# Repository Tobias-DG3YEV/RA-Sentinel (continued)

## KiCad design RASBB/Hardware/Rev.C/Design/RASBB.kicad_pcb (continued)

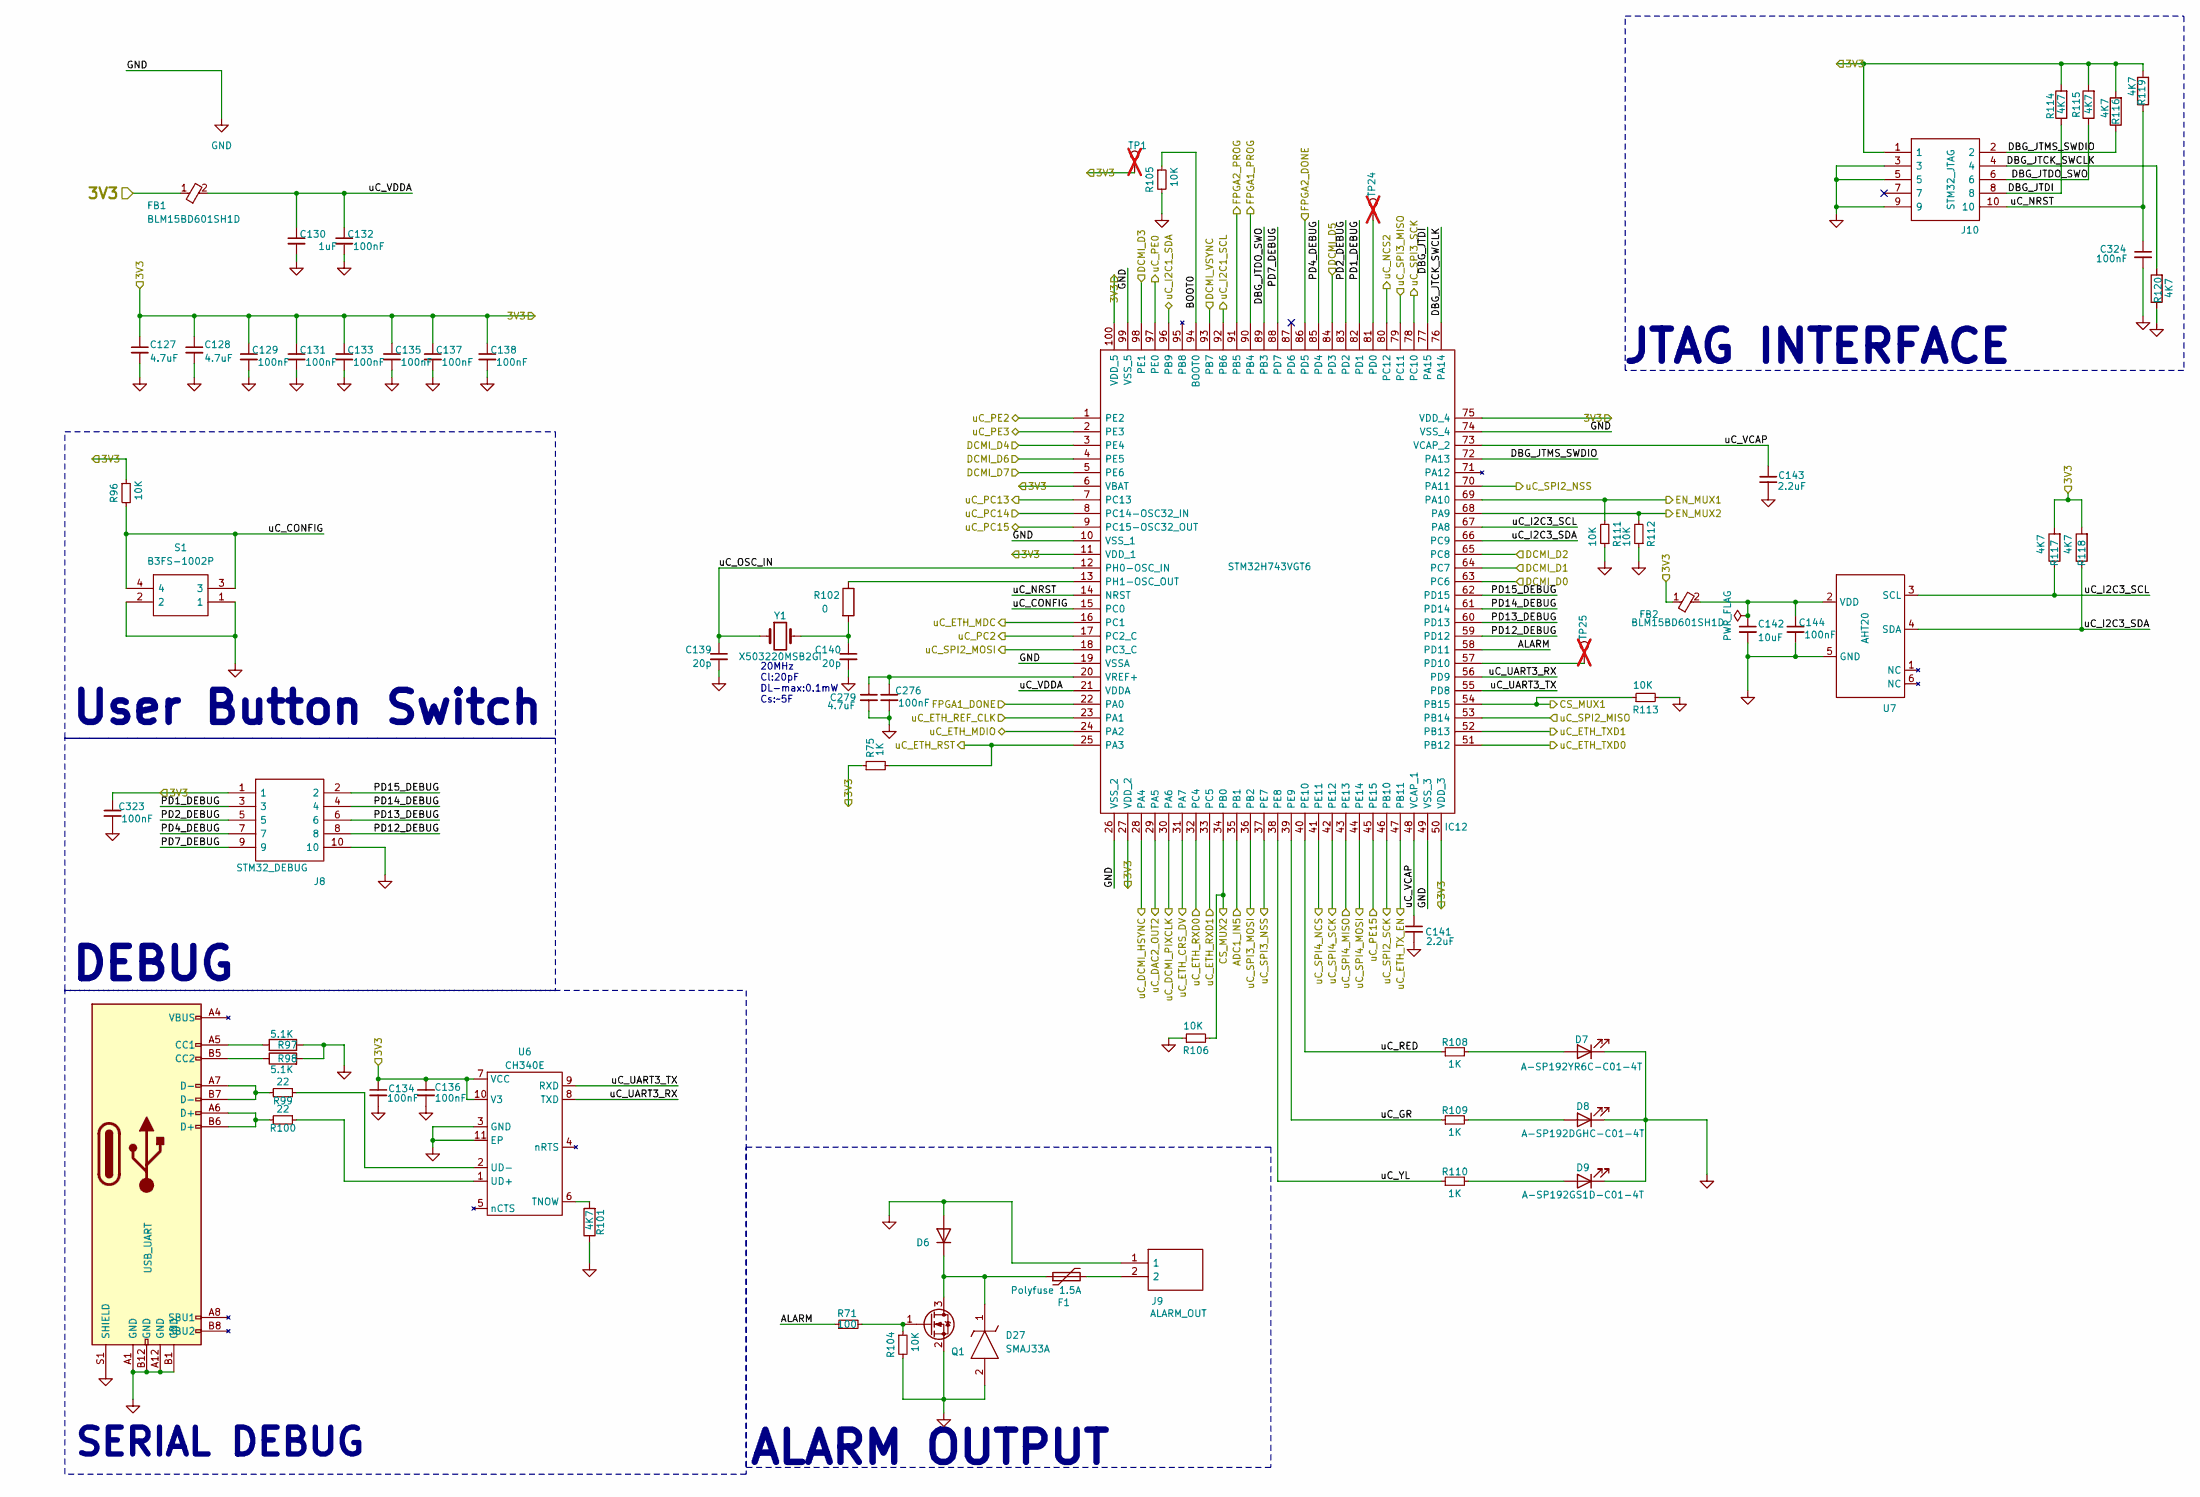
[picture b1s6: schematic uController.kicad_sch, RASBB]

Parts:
C127, C128, C279: 4.7uF; C_0603_1608Metric; Mfr. Part # GMK107BBJ475KA-T; LCSC Part # C7281848
C129, C131, C132, C133, C134, C135, C136, C137, C138, C144, C276, C323, C324: 100nF; C_0402_1005Metric; Mfr. Part # 0402B104K500CT; LCSC Part # C152814
C130: 1uF; C_0402_1005Metric; Mfr. Part # 0402X105M160CT; LCSC Part # C3889771
C139, C140: 20p; C_0402_1005Metric; Mfr. Part # 0402N200J500CT; LCSC Part # C123468
C141, C143: 2.2uF; C_0402_1005Metric; Mfr. Part # 0402X225M160CT; LCSC Part # C3905586
C142: 10uF; C_0402_1005Metric; Mfr. Part # 0402X106M100CT; LCSC Part # C2992625
D6: S210_R1_00001; D_SMB; Mfr. Part # S210_R1_00001; LCSC Part # C391676
D7: A-SP192YR6C-C01-4T; LED_0603_1608Metric; Mfr. Part # A-SP192YR6C-C01-4T; LCSC Part # C5355433
D8: A-SP192DGHC-C01-4T; LED_0603_1608Metric; Mfr. Part # A-SP192DGHC-C01-4T; LCSC Part # C19171301
D9: A-SP192GS1D-C01-4T; LED_0603_1608Metric; Mfr. Part # A-SP192GS1D-C01-4T; LCSC Part # C5355434
D27: SMAJ33A; DIOM5026X229N; Mouser Part Number 576-SMAJ33A
F1: Polyfuse 1.5A; BSMD1812; Mfr. Part # BSMD1812-150-33V; LCSC Part # C883154
FB1, FB2: BLM15BD601SH1D; NFZ15SG152SN10B; Mfr. Part # BLM15BD601SH1D; LCSC Part # C710334
IC12: STM32H743VGT6; QFP50P1600X1600X160-100N; Mfr. Part # STM32H743VGT6; LCSC Part # C730183
J7: USB_UART; USB_C_Receptacle_Palconn_UTC16-G; Mfr. Part # TYPE-C 16PIN 2MD(073); LCSC Part # C2765186
J8: STM32_DEBUG; PinHeader_2x05_P1.27mm_Vertical_SMD; Mfr. Part # ZX-PZ1.27-2-5PWZ; LCSC Part # C41370773
J9: ALARM_OUT; SHDRRA2W80P0X350_1X2_1050X920X750P; Mfr. Part # KF2EDGR-3.5-2P; LCSC Part # C441171
J10: STM32_JTAG; PinHeader_2x05_P1.27mm_Vertical_SMD; Mfr. Part # ZX-PZ1.27-2-5PWZ; LCSC Part # C41370773
Q1: DMN6075S; SOT-23; Mfr. Part # DMN6075S; LCSC Part # C5122015
R71: 100; R_0402_1005Metric; Mfr. Part # WR04X1000FTL; LCSC Part # C163808
R75, R108, R109, R110: 1K; R_0402_1005Metric; Mfr. Part # MR04X1001FTL; LCSC Part # C327796
R96, R104, R105, R106, R111, R112, R113: 10K; R_0402_1005Metric; Mfr. Part # WR04X1002FTL; LCSC Part # C163810
R97, R98: 5.1K; R_0402_1005Metric; Mfr. Part # WR04X512JTL; LCSC Part # C384321
R99, R100: 22; R_0402_1005Metric; Mfr. Part # WR04X22R0FTL; LCSC Part # C163821
R101, R114, R115, R116, R117, R118, R119, R120: 4K7; R_0402_1005Metric; Mfr. Part # WR04X4701FTL; LCSC Part # C163826
R102: 0; R_0402_1005Metric; Mfr. Part # MR04X000PTL; LCSC Part # C396825
S1: B3FS-1002P; B3FS-1000P; Mfr. Part # B3FS-1002P; LCSC Part # C271750
TP1, TP24, TP25: TestPoint; TestPoint_Pad_D1.0mm; not fitted
U6: CH340E; MSOP-10-1EP_3x3mm_P0.5mm_EP1.68x1.88mm; Mfr. Part # CH340E; LCSC Part # C99652
U7: AHT20; Mfr. Part # AHT20; LCSC Part # C2757850
Y1: X503220MSB2GI; Mfr. Part # X503220MSB2GI; LCSC Part # C112566

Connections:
/Audio_IN-OUT/3V3: C127.1, C128.1, C129.1, C131.1, C133.1, C134.1, C135.1, C136.1, C137.1, C138.1, C323.1, FB1.1, FB2.1, IC12.6 (VBAT), IC12.11 (VDD_1), IC12.27 (VDD_2), IC12.50 (VDD_3), IC12.75 (VDD_4), IC12.100 (VDD_5), J8.1, J10.1, R75.1, R96.1, R114.2, R115.2, R116.2, R117.2, R118.2, R119.2, TP1.1 (1_1), U6.7 (VCC), U6.10 (V3); also elsewhere on the board
/Audio_IN-OUT/Audio_PTT: IC12.45 (PE15); also elsewhere on the board
/CS2_FLASH_uC: IC12.80 (PC12); also elsewhere on the board
/CS_FLASH_uC: IC12.41 (PE11); also elsewhere on the board
/Config-SPI FLASH/MUX_EN1: IC12.69 (PA10), R111.2; also elsewhere on the board
/Config-SPI FLASH/MUX_EN2: IC12.68 (PA9), R112.2; also elsewhere on the board
/Config-SPI FLASH/SWITCH_FLASH_1: IC12.54 (PB15), R113.1; also elsewhere on the board
/Config-SPI FLASH/SWITCH_FLASH_2: IC12.34 (PB0), R106.2; also elsewhere on the board
/Ethernet_uC/ETH_RESET: IC12.25 (PA3), R75.2; also elsewhere on the board
/Ethernet_uC/RMII_MDC: IC12.16 (PC1); also elsewhere on the board
/Ethernet_uC/RMII_MDIO: IC12.24 (PA2); also elsewhere on the board
/Ethernet_uC/RMII_TX_EN: IC12.47 (PB11); also elsewhere on the board
/FPGA1_RESET: IC12.97 (PE0); also elsewhere on the board
/FPGA2_RESET: IC12.17 (PC2_C); also elsewhere on the board
/FPGA-01/BANK0/FPGA1_DONE: IC12.22 (PA0); also elsewhere on the board
/FPGA-01/FPGA1_PROG: IC12.90 (PB4); also elsewhere on the board
/FPGA-02/BANK0/FPGA2_DONE: IC12.86 (PD5); also elsewhere on the board
/FPGA-02/F2_B14_P15: IC12.98 (PE1); also elsewhere on the board
/FPGA-02/F2_B14_R15: IC12.3 (PE4); also elsewhere on the board
/FPGA-02/F2_B14_R16: IC12.4 (PE5); also elsewhere on the board
/FPGA-02/F2_B14_T15: IC12.5 (PE6); also elsewhere on the board
/FPGA-02/F2_B14_T16: IC12.28 (PA4); also elsewhere on the board
/FPGA-02/F2_B14_U14: IC12.64 (PC7); also elsewhere on the board
/FPGA-02/F2_B14_U16: IC12.30 (PA6); also elsewhere on the board
/FPGA-02/F2_B14_V14: IC12.63 (PC6); also elsewhere on the board
/FPGA-02/F2_B14_V15: IC12.65 (PC8); also elsewhere on the board
/FPGA-02/F2_B14_V16: IC12.84 (PD3); also elsewhere on the board
/FPGA-02/F2_B14_V17: IC12.93 (PB7); also elsewhere on the board
/FPGA-02/FPGA2_PROG: IC12.91 (PB5); also elsewhere on the board
/PCIE/PCIE_CS: IC12.37 (PE7); also elsewhere on the board
/PCIE/SMCLK: IC12.92 (PB6); also elsewhere on the board
/PCIE/SMDAT: IC12.96 (PB9); also elsewhere on the board
/RF_Transceiver/BUSY_LORA_G: IC12.8 (PC14-OSC32_IN); also elsewhere on the board
/RF_Transceiver/DIO1_LORA_G: IC12.1 (PE2); also elsewhere on the board
/RF_Transceiver/DIO2_LORA_G: IC12.2 (PE3); also elsewhere on the board
/RF_Transceiver/DIO3_LORA_G: IC12.9 (PC15-OSC32_OUT); also elsewhere on the board
/RF_Transceiver/NRST_LORA_G: IC12.7 (PC13); also elsewhere on the board
/RF_Transceiver/SPI_NSS_LORA_G: IC12.70 (PA11); also elsewhere on the board
/SO_FLASH_uC: IC12.43 (PE13); also elsewhere on the board
/uController/ADC1_IN5: IC12.35 (PB1); also elsewhere on the board
/uController/ALARM: IC12.58 (PD11), R71.1
/uController/BOOT0: IC12.94 (BOOT0), R105.1
/uController/DBG_JTCK_SWCLK: IC12.76 (PA14), J10.4, R120.2
/uController/DBG_JTDI: IC12.77 (PA15), J10.8, R114.1
/uController/DBG_JTDO_SWO: IC12.89 (PB3), J10.6, R115.1
/uController/DBG_JTMS_SWDIO: IC12.72 (PA13), J10.2, R116.1
/uController/PD1_DEBUG: IC12.82 (PD1), J8.3
/uController/PD2_DEBUG: IC12.83 (PD2), J8.5
/uController/PD4_DEBUG: IC12.85 (PD4), J8.7
/uController/PD7_DEBUG: IC12.88 (PD7), J8.9
/uController/PD12_DEBUG: IC12.59 (PD12), J8.8
/uController/PD13_DEBUG: IC12.60 (PD13), J8.6
/uController/PD14_DEBUG: IC12.61 (PD14), J8.4
/uController/PD15_DEBUG: IC12.62 (PD15), J8.2
/uController/uC_CONFIG: IC12.15 (PC0), R96.2, S1.3, S1.4
/uController/uC_DAC2_OUT2: IC12.29 (PA5); also elsewhere on the board
/uController/uC_ETH_CRS_DV: IC12.31 (PA7); also elsewhere on the board
/uController/uC_ETH_REF_CLK: IC12.23 (PA1); also elsewhere on the board
/uController/uC_ETH_RXD0: IC12.32 (PC4); also elsewhere on the board
/uController/uC_ETH_RXD1: IC12.33 (PC5); also elsewhere on the board
/uController/uC_ETH_TXD0: IC12.51 (PB12); also elsewhere on the board
/uController/uC_ETH_TXD1: IC12.52 (PB13); also elsewhere on the board
/uController/uC_GR: IC12.39 (PE9), R109.1
/uController/uC_I2C3_SCL: IC12.67 (PA8), R117.1, U7.3 (SCL)
/uController/uC_I2C3_SDA: IC12.66 (PC9), R118.1, U7.4 (SDA)
/uController/uC_NRST: C324.1, IC12.14 (NRST), J10.10, R119.1
/uController/uC_OSC_IN: C139.1, IC12.12 (PH0-OSC_IN), Y1.1
/uController/uC_RED: IC12.40 (PE10), R108.1
/uController/uC_SPI2_MISO: IC12.53 (PB14); also elsewhere on the board
/uController/uC_SPI2_MOSI: IC12.18 (PC3_C); also elsewhere on the board
/uController/uC_SPI2_SCK: IC12.46 (PB10); also elsewhere on the board
/uController/uC_SPI3_MISO: IC12.79 (PC11); also elsewhere on the board
/uController/uC_SPI3_MOSI: IC12.36 (PB2); also elsewhere on the board
/uController/uC_SPI3_SCK: IC12.78 (PC10); also elsewhere on the board
/uController/uC_SPI4_MOSI: IC12.44 (PE14); also elsewhere on the board
/uController/uC_SPI4_SCK: IC12.42 (PE12); also elsewhere on the board
/uController/uC_UART3_RX: IC12.56 (PD9), U6.8 (TXD)
/uController/uC_UART3_TX: IC12.55 (PD8), U6.9 (RXD)
/uController/uC_VCAP: C141.1, C143.1, IC12.48 (VCAP_1), IC12.73 (VCAP_2)
/uController/uC_VDDA: C130.1, C132.1, FB1.2, IC12.21 (VDDA)
/uController/uC_YL: IC12.38 (PE8), R110.1
GND: C127.2, C128.2, C129.2, C130.2, C131.2, C132.2, C133.2, C134.2, C135.2, C136.2, C137.2, C138.2, C139.2, C140.2, C141.2, C142.2, C143.2, C144.2, C276.2, C279.2, C323.2, C324.2, D6.2 (A), D7.1 (K), D8.1 (K), D9.1 (K), D27.2, IC12.10 (VSS_1), IC12.19 (VSSA), IC12.26 (VSS_2), IC12.49 (VSS_3), IC12.74 (VSS_4), IC12.99 (VSS_5), J7.A1 (GND), J7.A12 (GND), J7.B1 (GND), J7.B12 (GND), J7.S1 (SHIELD), J8.10, J9.1, J10.3, J10.5, J10.9, Q1.2 (S), R97.2, R98.2, R101.1, R104.2, R105.2, R106.1, R111.1, R112.1, R113.2, R120.1, S1.1, S1.2, U6.3 (GND), U6.11 (EP), U7.5 (GND); also elsewhere on the board
unnamed: C140.1, R102.2, Y1.2
unnamed: D6.1 (K), D27.1, F1.1, Q1.3 (D)
unnamed: D7.2 (A), R108.2
unnamed: D8.2 (A), R109.2
unnamed: D9.2 (A), R110.2
unnamed: F1.2, J9.2
unnamed: IC12.81 (PD0), TP24.1 (1_1)
unnamed: IC12.57 (PD10), TP25.1 (1_1)
unnamed: IC12.13 (PH1-OSC_OUT), R102.1
unnamed: C276.1, C279.1, IC12.20 (VREF+)
unnamed: J7.A5 (CC1), R97.1
unnamed: J7.B5 (CC2), R98.1
unnamed: J7.A6 (D+), J7.B6 (D+), R100.2
unnamed: J7.A7 (D-), J7.B7 (D-), R99.2
unnamed: Q1.1 (G), R71.2, R104.1
unnamed: R101.2, U6.6 (TNOW)
unnamed: R100.1, U6.1 (UD+)
unnamed: R99.1, U6.2 (UD-)
unnamed: C142.1, C144.1, FB2.2, U7.2 (VDD)

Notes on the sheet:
20MHz Cl:20pF DL-max:0.1mW Cs:~5F
DEBUG
SERIAL DEBUG
User Button Switch
ALARM OUTPUT
JTAG INTERFACE

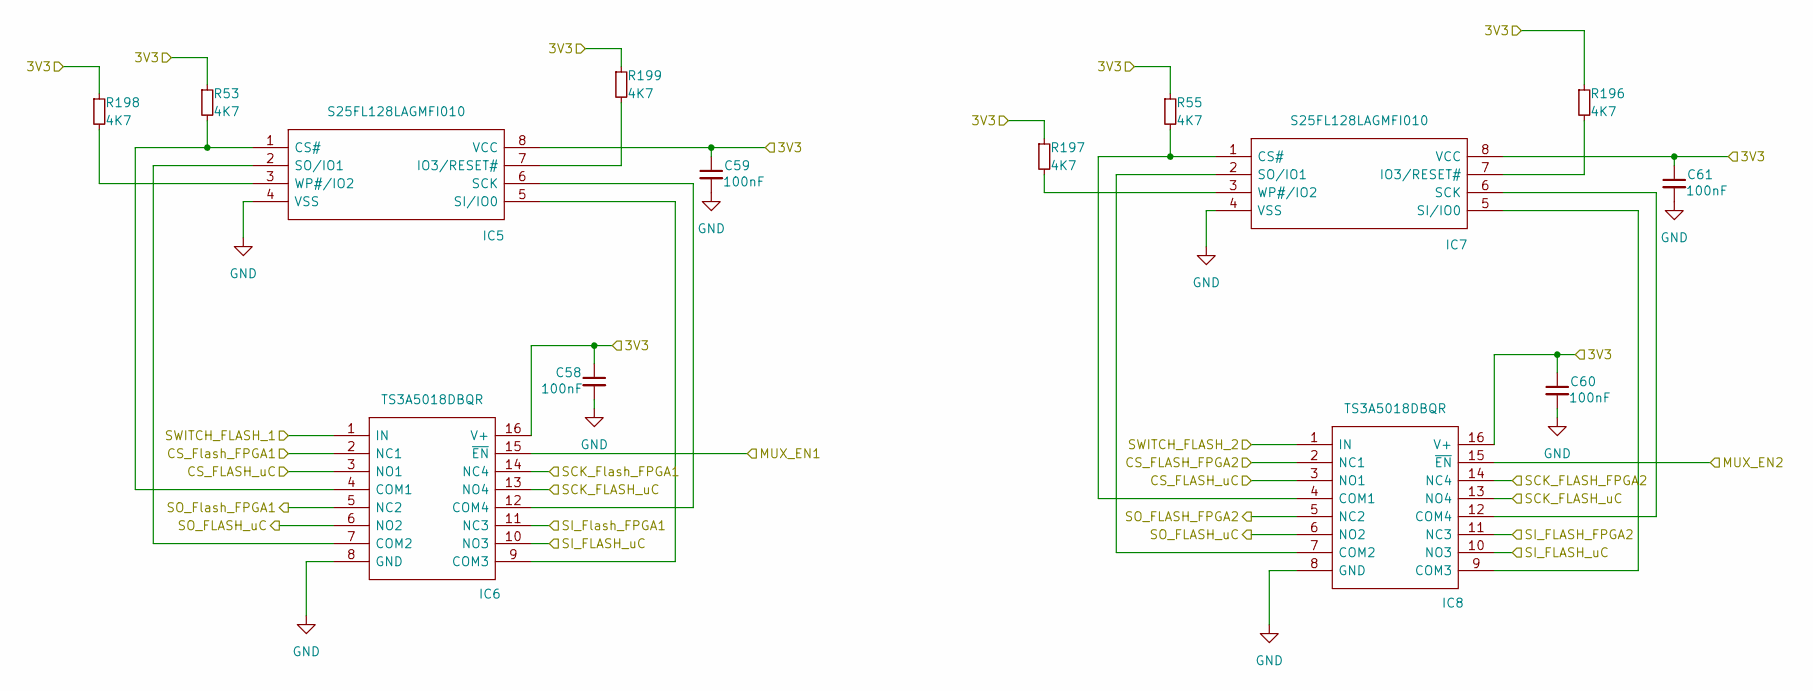
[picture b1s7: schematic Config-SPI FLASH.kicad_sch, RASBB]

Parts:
C58, C59, C60, C61: 100nF; C_0402_1005Metric; Mfr. Part # 0402B104K500CT; LCSC Part # C152814
IC5, IC7: S25FL128LAGMFI010; SOIC127P800X216-8N; Mfr. Part # S25FL128LAGMFI010; LCSC Part # C2959152
IC6, IC8: TS3A5018DBQR; SOP64P600X175-16N; Mfr. Part # TS3A5018DBQR; LCSC Part # C202285
R53, R55, R196, R197, R198, R199: 4K7; R_0402_1005Metric; Mfr. Part # WR04X4701FTL; LCSC Part # C163826

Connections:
/Audio_IN-OUT/3V3: C58.1, C59.1, C60.1, C61.1, IC5.8 (VCC), IC6.16 (V+), IC7.8 (VCC), IC8.16 (V+), R53.1, R55.1, R196.1, R197.1, R198.1, R199.1; also elsewhere on the board
/CS_FLASH_FPGA2: IC8.2 (NC1); also elsewhere on the board
/CS_FLASH_uC: IC6.3 (NO1), IC8.3 (NO1); also elsewhere on the board
/Config-SPI FLASH/CS_Flash_FPGA1: IC6.2 (NC1); also elsewhere on the board
/Config-SPI FLASH/MUX_EN1: IC6.15 (~EN); also elsewhere on the board
/Config-SPI FLASH/MUX_EN2: IC8.15 (~EN); also elsewhere on the board
/Config-SPI FLASH/SCK_FLASH_FPGA2: IC8.14 (NC4); also elsewhere on the board
/Config-SPI FLASH/SCK_Flash_FPGA1: IC6.14 (NC4); also elsewhere on the board
/Config-SPI FLASH/SI_FLASH_FPGA2: IC8.11 (NC3); also elsewhere on the board
/Config-SPI FLASH/SI_Flash_FPGA1: IC6.11 (NC3); also elsewhere on the board
/Config-SPI FLASH/SO_FLASH_FPGA2: IC8.5 (NC2); also elsewhere on the board
/Config-SPI FLASH/SO_Flash_FPGA1: IC6.5 (NC2); also elsewhere on the board
/Config-SPI FLASH/SWITCH_FLASH_1: IC6.1 (IN); also elsewhere on the board
/Config-SPI FLASH/SWITCH_FLASH_2: IC8.1 (IN); also elsewhere on the board
/SCK_FLASH_uC: IC6.13 (NO4), IC8.13 (NO4); also elsewhere on the board
/SI_FLASH_uC: IC6.10 (NO3), IC8.10 (NO3); also elsewhere on the board
/SO_FLASH_uC: IC6.6 (NO2), IC8.6 (NO2); also elsewhere on the board
GND: C58.2, C59.2, C60.2, C61.2, IC5.4 (VSS), IC6.8 (GND), IC7.4 (VSS), IC8.8 (GND); also elsewhere on the board
unnamed: IC5.1 (CS#), IC6.4 (COM1), R53.2
unnamed: IC5.7 (IO3/RESET#), R199.2
unnamed: IC5.6 (SCK), IC6.12 (COM4)
unnamed: IC5.5 (SI/IO0), IC6.9 (COM3)
unnamed: IC5.2 (SO/IO1), IC6.7 (COM2)
unnamed: IC5.3 (WP#/IO2), R198.2
unnamed: IC7.1 (CS#), IC8.4 (COM1), R55.2
unnamed: IC7.7 (IO3/RESET#), R196.2
unnamed: IC7.6 (SCK), IC8.12 (COM4)
unnamed: IC7.5 (SI/IO0), IC8.9 (COM3)
unnamed: IC7.2 (SO/IO1), IC8.7 (COM2)
unnamed: IC7.3 (WP#/IO2), R197.2

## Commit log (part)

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2024-03-11 2.4GHz RF Front-End PCB Rev. A
    First check-in of the 2.GHz Radio Front-End Rev. A. This first version is regarded as a EVM, Evaluation Module which uses a dual PMOD interface to send the I+Q data via LVDS to a FPGA ve. board like 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
2024-05-15 Updated README.md
    Some clarifications of the digital baseband signal path.
2024-05-15 Update README.md
    Add link to the FPGA board supplier.
2024-06-01 Renamed folder from WiFiADC to RFFE2400_PCB
2024-06-01 Added info for PCB design files, layout changes
2024-06-01 added RASM2400 Block Diagram
2024-06-02 updated Verilog code of RASM2400, added Vivado project zip
2024-06-02 added RASM2400 HDMI monitor screenshot
2024-06-02 added HDMI Screenshot to readme.md
2024-06-02 added hardware photo
2024-06-02 updated RASM2400 block diagram
2024-06-04 V1.01 added auto decaying peak level
2024-06-04 V1.01 added Vivado project in -zip and .bit file of V1.01
2024-06-04 added firmware for the HKU, Houskeeping unit of the RFFE daughter board
2024-06-04 Cosmetic updates on the RASM2400 Verilog files.
2024-07-05 Updated README.md - small typo
2024-10-01 added owifi_rx (my implementation of openOFDM incl. SPI slave interface and DCMI meta data streaming master) and RASWECU (STM32H7xx firmware writing to the FPGA configuration registers and a DCMI sla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
2024-10-13 Status Update deliverable #2
2025-01-28 Added Readme.md
2025-01-28 1. Update readme.md
2025-01-28 Added RASBB_preview.JPG
2025-01-28 Update RASBB basic features list
2025-01-28 Added block diagram of RASBB
2025-01-28 RASBB Block diagram added to the readme.md
2025-02-08 Added Revision A of RASBB board layout
2025-02-08 Added KiCAD design files of RASBB Rev. A
2025-02-14 THT parts added
2025-02-15 Update readme.md
    Update block diagram
2025-02-16 Update readme.md
    updated read me
2025-02-16 Delete RASBB/RASBB_preview.JPG
    deleted file/uploads new preview
2025-02-16 Delete RASBB/RASBB Board Layout.svg
    deleted/updated new board view
2025-02-16 Delete RASBB/PCB_Design directory
    deleted, will add the latest version
2025-02-16 Delete RASBB/Rev.A directory
    deleted/will add new one
2025-02-16 Update readme.md
    Revise read me
2025-02-16 Add block diagrams
2025-02-16 RASBB Project Files
2025-02-16 Rename readme.md to README.md
2025-02-21 Updated current state section
2025-02-22 RASRF-RevA
    Uploaded RASRF-RevA
2025-02-22 Update README.md
    Added 3D view of RASRF-RevA
2025-02-23 Added first Revision of the RASBB board.
2025-02-23 Initial commit of the RASBB AP_FPGA software folder.
2025-02-23 Added confrimed BOM of RASBB Rev.A received from the PCBA.
2025-02-23 Added RASRF, the 2.4GHz wide band radio front-end for the RA-Sentinel project.
2025-02-23 Added RASBB uController firmware.
2025-02-24 Update Findings_RevA.md from first Rev. A inspection.
2025-02-24 Update Findings_RevA.md, 1V DC DC eanble pin
2025-02-25 Initial check-in of the AP_FPGA sources.
2025-02-27 Added photo of RASBB-RASRF2400WB prototype Rev. A.
2025-02-27 Changed hardware photo in README.md
    Changed the old photo of the QMTech FPGA board and PMOD Front-End PCB to the new designed hardware.
2025-02-27 Update README.md with new prototype description.
2025-02-27 Update README.md: Fixed links of the image files.
    redirected the relative path to https://raw.githubusercontent.com/Tobias-DG3YEV/RA-Sentinel/main/
2025-02-28 Corrected the RASRF_2400WB PCB design files. They where not the latest from Rev. A. sent to manufacturer.
2025-03-23 Added photos of real hardware prototype Rev. A.
2025-04-06 added LVDS Test code
2025-04-06 RASBB Rev B
    Read Findings_RevA.md to track changes from Rev A to Rev B
2025-04-06 Added REvision B of the RASBB board
2025-04-09 Corrected the directory structure of RASBB/Rev.B.
2025-04-09 Corrected the location of the design files for RASBB/Rev.B
2025-04-09 updated design files
2025-04-12 Added Test Results of the first bring-up of the Revision A board.
2025-04-13 Update Findings_RevA.md
    update to correct 2nd flash connection to fpga 2
2025-04-13 Update HardwareTestResults.md
    added USB-C tested
2025-04-13 Rev B
    Config Flash 2 modified, Termination added to LVDS lines
2025-04-13 Delete RASBB/Hardware/Rev.B/Design/uController.kicad_sch-bak
    back up file deleted
2025-04-17 Updated RASBB Rev. A. photo
2025-04-20 Added ECUTEST für STM32, Ethernet and SPI Connection towards FPGA1 and 2
2025-04-20 Added FPGA_TEST, a versatile test quite for the Analog FPGA.
2025-04-20 Added the Dgitgal Front end project folder and the basic DP_FPGA test for ruther extentions.
2025-04-20 Updated licecnsing information and link to the nlnet project page.
2025-04-20 Added link to project page.
2025-04-20 renamed Software/FPGA_TEST/ to Software/AP_FPGA_TEST/
2025-04-24 Update Findings_RevA.md
    closed ID 25
2025-04-24 correct Ethernet pinouts issue
2025-04-24 corrected the Ethernet pinouts
2025-04-24 Production data
    Ethernet pinouts fixed
2025-04-24 Delete RASBB/Hardware/Rev.B/Design/RASBB-B.zip
    should be removed from here, since it is already in the upper folder
2025-04-24 RASBB-RevB.zip overwritten by never RASBB-B.zip
2025-07-12 Update Findings_RevA.md
    Added DDR3 RAm missing address line pin
2025-07-24 Create RASRF2400WBMC
2025-07-26 Update RASRF2400WBMC
2025-11-29 Add finding for LO Phase Sync over Ethernet
    Added a new finding regarding LO Phase Sync over Ethernet.
2025-12-13 Added NGI and NLnet Logos and links
2025-12-15 Added new Firmware project for RASBB ECU (STM32H743) containing UPNP and config webserver.
2025-12-15 Added "Latest Udpates"
2025-12-15 Added images folder and config interface screenshots
2025-12-15 reorganised images into /Images folder
2025-12-15 images update
2025-12-15 Updated image links
2025-12-15 Added Images/SuspEdit.png Suspect Edit sceenshot.
2025-12-15 Added documentation about the config GUI
2026-01-04 Add clock syncronisation facilities
2026-05-05 Added open viterbi decoder. Code is not yet functional. Puncturing is missing.
2026-05-05 Added foto of RASANT2400 prototype.
2026-05-14 Modify links and images in README.md
    Updated funding and project links in README.
2026-05-14 Re-structure ReadMe to have better visibility on projects
2026-05-14 Update README with new image links and descriptions
2026-05-14 Enhance structure for better readibility
2026-05-16 Update Design_Notes.md
    Added AoA basic principle description.
2026-05-17 Modify PCB name in design notes
2026-05-17 Update project maintainer information in README
2026-05-17 Revise README with project updates and funding info
    Updated project description, added funding details, and improved formatting.
2026-05-17 Fix typos and formatting in README.md for better readibility
    Corrected spelling and formatting issues in the README.
2026-05-17 Added license file to RASANT2400.
2026-05-17 Added fotos of the Rev. A protoype of RASRF2400WB.
2026-05-17 Flipped front image of RASRF2400WB. Added '.gitignore' file.
2026-05-23 Add links to related RA-Sentinel boards in README
2026-05-23 Changed license to CERN Open Hardware Licence Version 2 - Strongly Reciprocal. Changed position of the logos on PCB.
2026-05-30 added license note on silkscreen removed older RASBB revision
2026-05-30 Dublicated-Delete RASBB/Hardware/Rev.A/MfgData directory
    Production files under producation folder
2026-05-30 Cleaned up license files. Now software licenses are defined in LICENSE.SW.TXT and for hardware LICENSE.HW.TXT unless there is already a derived licenses.
2026-05-30 Updated license files.
2026-05-30 Added license files.
2026-05-31 RASBB Findings: Add shunt resistor and header for power measurement
    Added a shunt resistor and header for measuring power consumption at the PCIE connector.
2026-05-31 Updated RASANT PCB
2026-05-31 Updated RASANT2400 PCB.
2026-06-01 Update on select files for REUSE Specification (NGI0/FSFE)
2026-06-07 Update findings to reflect closed issues
2026-06-12 Added fotos of RASANT2400 and RASRF2400WBMC.
2026-06-14 Change PCB section to PCBA with new images
    Updated PCB section to PCBA and added images for top and bottom sides.
2026-06-14 Update status in README to reflect successful PCBA tests
2026-06-25 Udpated version Rev C with opeoinmg in the solder mask to allow soldering of SMA connectors.
2026-06-30 Update README with RASANT2400 project information
    Added RASANT2400 antenna project details to README.
2026-06-30 Fix link for RASANT2400 in README.md
